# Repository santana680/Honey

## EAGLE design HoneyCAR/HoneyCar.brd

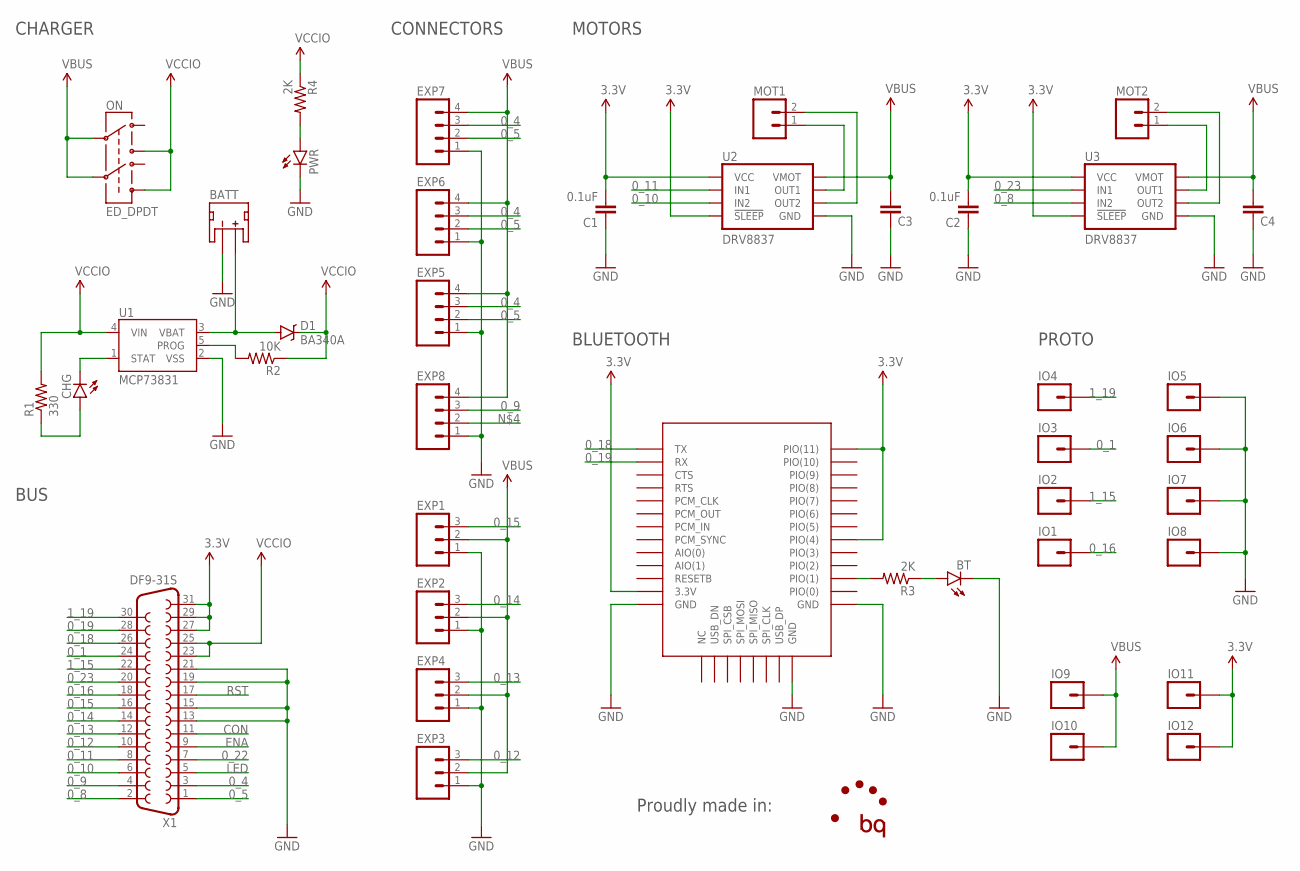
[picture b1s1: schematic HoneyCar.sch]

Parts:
BATT: JST_2MM_MALE; JST-2-SMD
BT: LED0603; LED-0603
C1, C2, C3, C4: 0.1uF; 0603-CAP
CHG: LED0603; LED-0603
D1: BA340A; SMA-DIODE
EXP1, EXP2, EXP3, EXP4: M03LOCK; 1X03_LOCK
EXP5, EXP6, EXP7, EXP8: M04JST; 1X04-1.5MM_JST
IC1: BC04_BLUETOOTH; BC04
IO1, IO2, IO3, IO4, IO5, IO6, IO7, IO8, IO9, IO10, IO11, IO12: M01PTH_LONGPAD; 1X01_LONGPAD
MOT1, MOT2: M02POLAR; MOLEX-1X2
ON: ED_DPDT
PWR: LED0603; LED-0603
R1: 330; R0402
R2: 10K; R0402
R3, R4: 2K; R0402
U1: MCP73831; SOT23-5
U2, U3: DRV8837; DSG
X1: DF9-31S

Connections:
0_1: IO3.1, X1.24
0_4: EXP5.3, EXP6.3, EXP7.3, X1.3
0_5: EXP5.2, EXP6.2, EXP7.2, X1.1
0_8: U3.5 (IN2), X1.2
0_9: EXP8.3, X1.4
0_10: U2.5 (IN2), X1.6
0_11: U2.6 (IN1), X1.8
0_12: EXP3.3, X1.10
0_13: EXP4.3, X1.12
0_14: EXP2.3, X1.14
0_15: EXP1.3, X1.16
0_16: IO1.1, X1.18
0_18: IC1.P$1 (TX), X1.26
0_19: IC1.P$2 (RX), X1.28
0_22: X1.7
0_23: U3.6 (IN1), X1.20
1_15: IO2.1, X1.22
1_19: IO4.1, X1.30
3.3V: C1.2, C2.2, IC1.P$12 (3.3V), IC1.P$27 (PIO(4)), IC1.P$34 (PIO(11)), IO11.1, IO12.1, U2.7 (!SLEEP), U2.8 (VCC), U3.7 (!SLEEP), U3.8 (VCC), X1.27, X1.29, X1.31
CON: X1.11
ENA: X1.9
GND: BATT.1 (-), BT.C, C1.1, C2.1, C3.1, C4.1, EXP1.1, EXP2.1, EXP3.1, EXP4.1, EXP5.1, EXP6.1, EXP7.1, EXP8.1, IC1.P$13 (GND), IC1.P$21 (GND), IC1.P$22 (GND), IO5.1, IO6.1, IO7.1, IO8.1, PWR.C, U1.2 (VSS), U2.4 (GND), U2.PAD (GND), U3.4 (GND), U3.PAD (GND), X1.13, X1.15, X1.19, X1.21
LED: X1.5
unnamed: IC1.P$24 (PIO(1)), R3.2
unnamed: BT.A, R3.1
unnamed: PWR.A, R4.2
unnamed: CHG.C, U1.1 (STAT)
unnamed: CHG.A, R1.1
unnamed: R2.2, U1.5 (PROG)
unnamed: BATT.2 (+), D1.A, U1.3 (VBAT)
unnamed: MOT1.1, U2.2 (OUT1)
unnamed: MOT1.2, U2.3 (OUT2)
unnamed: MOT2.1, U3.2 (OUT1)
unnamed: MOT2.2, U3.3 (OUT2)
RST: X1.17
VBUS: C3.2, C4.2, EXP1.2, EXP2.2, EXP3.2, EXP4.2, EXP5.4, EXP6.4, EXP7.4, EXP8.4, IO9.1, IO10.1, ON.2, ON.5, U2.1 (VMOT), U3.1 (VMOT)
VCCIO: D1.C, ON.3, ON.6, R1.2, R2.1, R4.1, U1.4 (VIN), X1.23, X1.25

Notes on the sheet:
CHARGER
BUS
MOTORS
CONNECTORS
BLUETOOTH
Proudly made in:
PROTO

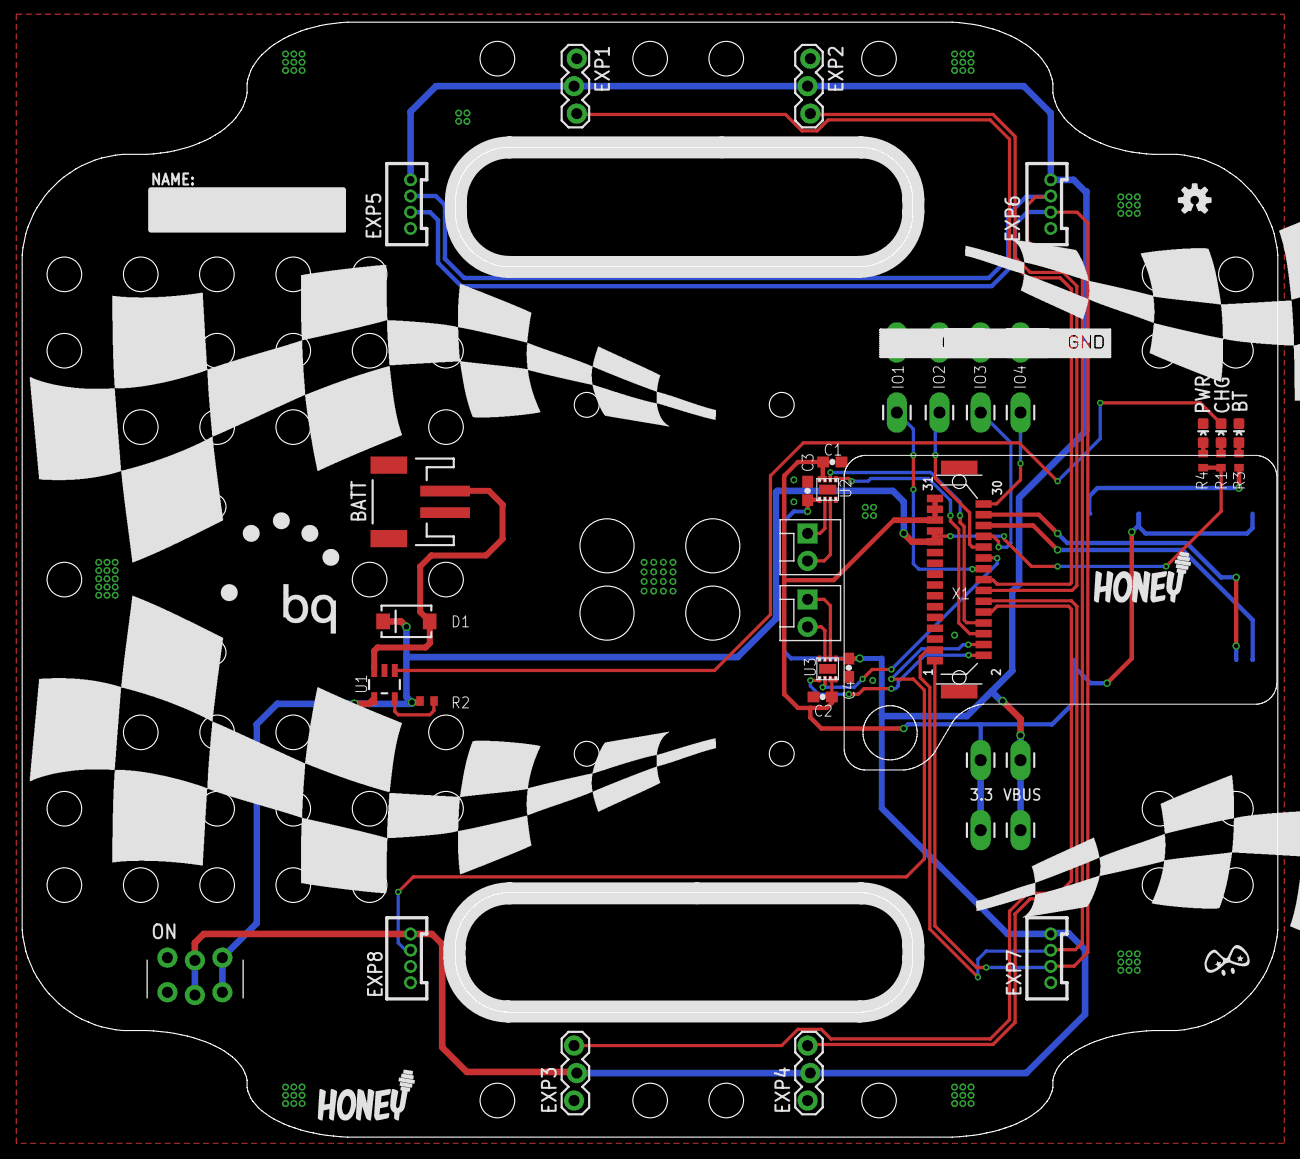
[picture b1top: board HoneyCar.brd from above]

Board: 2 copper layers, 116.1 x 103.1 mm, 52 parts (1 on the bottom side), 32 nets.

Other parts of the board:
LOGO1: OSHW-LOGOS; OSHW-LOGO-S
U$5, U$7: LOGO_MEDIUM
U$8: BQ_LOGO
U$9: PIGHIXXX_LOGO
U$10, U$11, U$12: S_KICIK_GND_1
U$14, U$15, U$16: CAR_RACING_BIG

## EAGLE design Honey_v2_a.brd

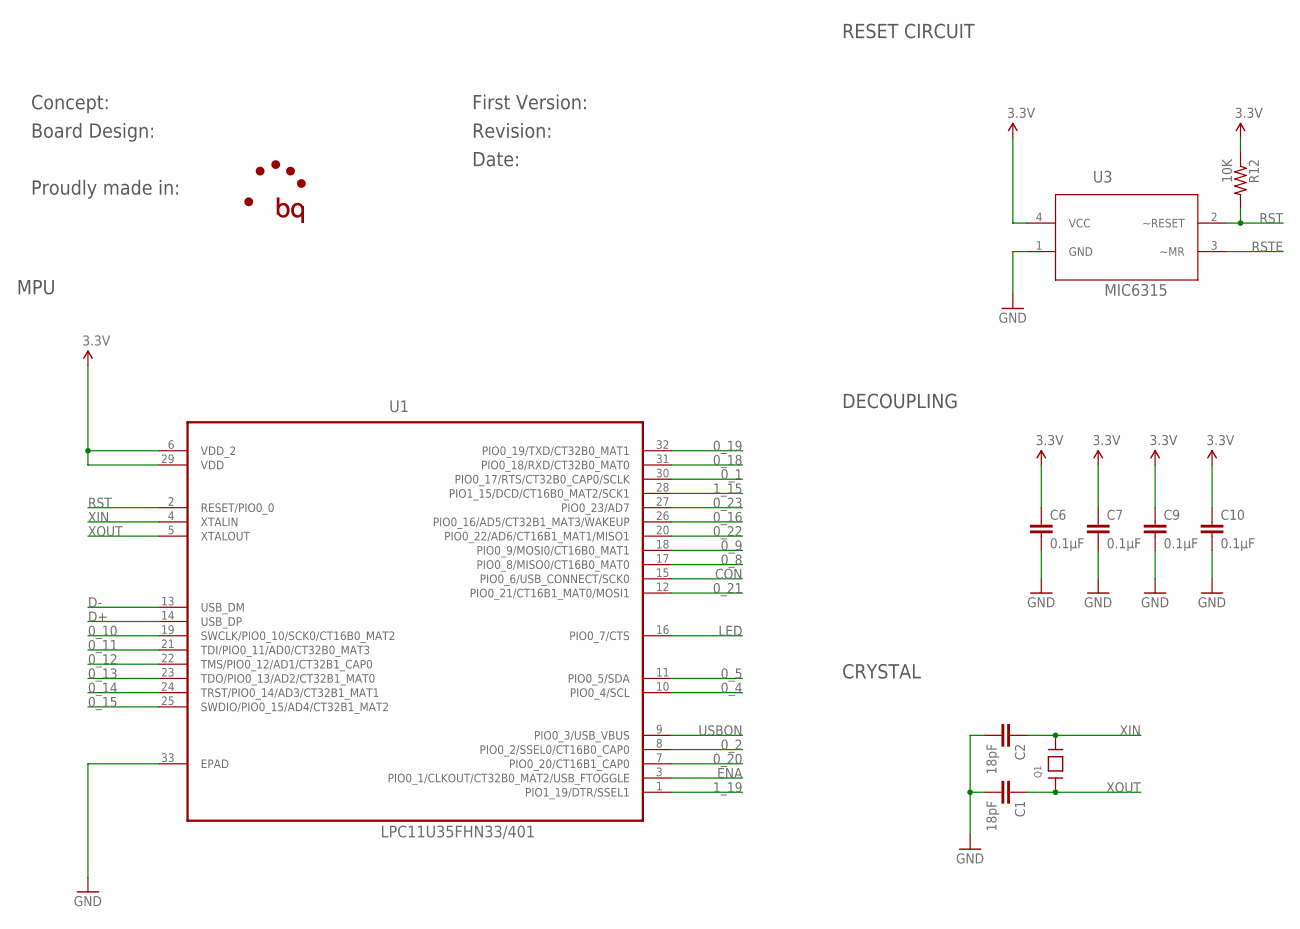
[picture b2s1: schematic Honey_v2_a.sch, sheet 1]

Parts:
C1, C2: 18pF; C0402
C6, C7, C9, C10: 0.1µF; C0402
Q1: 12MHz 4 pad crystal 3.2x2.5; CRYSTAL_3.2X2.5
R12: 10K; R0402
U1: LPC11U35FHN33/401; QFN65P700X700X100-33N
U3: MIC6315; SOT-143B

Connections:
0_1: U1.30 (PIO0_17/RTS/CT32B0_CAP0/SCLK); also elsewhere on the board
0_2: U1.8 (PIO0_2/SSEL0/CT16B0_CAP0)
0_4: U1.10 (PIO0_4/SCL); also elsewhere on the board
0_5: U1.11 (PIO0_5/SDA); also elsewhere on the board
0_8: U1.17 (PIO0_8/MISO0/CT16B0_MAT0); also elsewhere on the board
0_9: U1.18 (PIO0_9/MOSI0/CT16B0_MAT1); also elsewhere on the board
0_10: U1.19 (SWCLK/PIO0_10/SCK0/CT16B0_MAT2); also elsewhere on the board
0_11: U1.21 (TDI/PIO0_11/AD0/CT32B0_MAT3); also elsewhere on the board
0_12: U1.22 (TMS/PIO0_12/AD1/CT32B1_CAP0); also elsewhere on the board
0_13: U1.23 (TDO/PIO0_13/AD2/CT32B1_MAT0); also elsewhere on the board
0_14: U1.24 (TRST/PIO0_14/AD3/CT32B1_MAT1); also elsewhere on the board
0_15: U1.25 (SWDIO/PIO0_15/AD4/CT32B1_MAT2); also elsewhere on the board
0_16: U1.26 (PIO0_16/AD5/CT32B1_MAT3/WAKEUP); also elsewhere on the board
0_18: U1.31 (PIO0_18/RXD/CT32B0_MAT0); also elsewhere on the board
0_19: U1.32 (PIO0_19/TXD/CT32B0_MAT1); also elsewhere on the board
0_20: U1.7 (PIO0_20/CT16B1_CAP0)
0_21: U1.12 (PIO0_21/CT16B1_MAT0/MOSI1)
0_22: U1.20 (PIO0_22/AD6/CT16B1_MAT1/MISO1); also elsewhere on the board
0_23: U1.27 (PIO0_23/AD7); also elsewhere on the board
1_15: U1.28 (PIO1_15/DCD/CT16B0_MAT2/SCK1); also elsewhere on the board
1_19: U1.1 (PIO1_19/DTR/SSEL1); also elsewhere on the board
3.3V: C6.1, C7.1, C9.1, C10.1, R12.1, U1.6 (VDD_2), U1.29 (VDD), U3.4 (VCC); also elsewhere on the board
CON: U1.15 (PIO0_6/USB_CONNECT/SCK0); also elsewhere on the board
D+: U1.14 (USB_DP); also elsewhere on the board
D-: U1.13 (USB_DM); also elsewhere on the board
ENA: U1.3 (PIO0_1/CLKOUT/CT32B0_MAT2/USB_FTOGGLE); also elsewhere on the board
GND: C1.2, C2.2, C6.2, C7.2, C9.2, C10.2, U1.33 (EPAD), U3.1 (GND); also elsewhere on the board
LED: U1.16 (PIO0_7/CTS); also elsewhere on the board
RST: R12.2, U1.2 (RESET/PIO0_0), U3.2 (~RESET); also elsewhere on the board
RSTE: U3.3 (~MR); also elsewhere on the board
USBON: U1.9 (PIO0_3/USB_VBUS); also elsewhere on the board
XIN: C2.1, Q1.3, U1.4 (XTALIN)
XOUT: C1.1, Q1.1, U1.5 (XTALOUT)

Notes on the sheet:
MPU
RESET CIRCUIT
DECOUPLING
CRYSTAL
Concept:
Board Design:
Proudly made in:
First Version:
Revision:
Date:

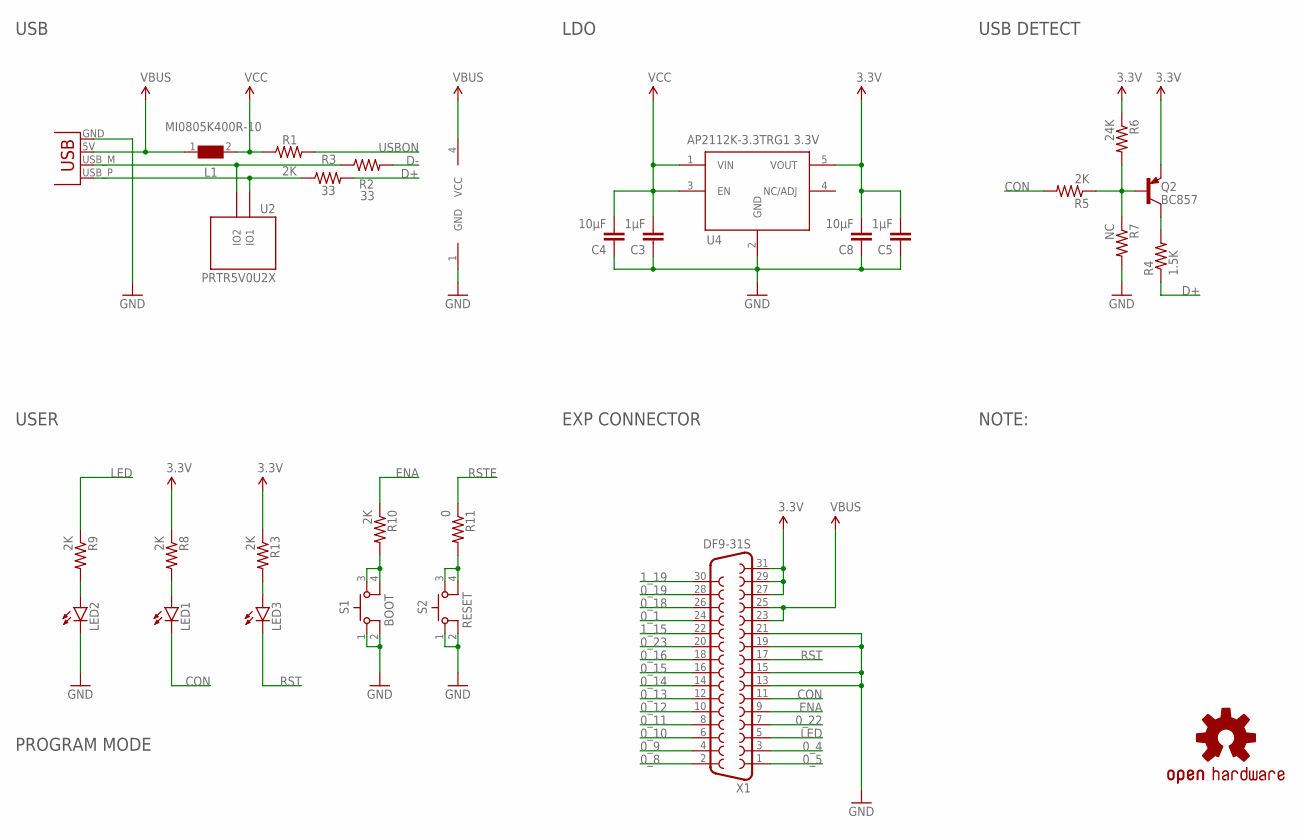
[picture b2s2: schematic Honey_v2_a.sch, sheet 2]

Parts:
C3, C5: 1µF; 0603-CAP
C4, C8: 10µF; 0603-CAP
J1: USBPCB; USB-A-PCB
L1: MI0805K400R-10; 0805
LED1, LED2, LED3: LED0603; LED-0603
LOGO1: OSHW-LOGOS; OSHW-LOGO-S
Q2: BC857; SOT23-BEC
R1, R5, R8, R9, R10, R13: 2K; R0402
R2, R3: 33; R0603
R4: 1.5K; R0402
R6: 24K; R0402
R7: NC; R0402
R11: 0; R0402
S1: BOOT; MINI_PUSHBUTTON
S2: RESET; MINI_PUSHBUTTON
U2: PRTR5V0U2X; SOT-143B
U4: AP2112K-3.3TRG1 3.3V; SOT23-5
X1: DF9-31S

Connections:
0_1: X1.24; also elsewhere on the board
0_4: X1.3; also elsewhere on the board
0_5: X1.1; also elsewhere on the board
0_8: X1.2; also elsewhere on the board
0_9: X1.4; also elsewhere on the board
0_10: X1.6; also elsewhere on the board
0_11: X1.8; also elsewhere on the board
0_12: X1.10; also elsewhere on the board
0_13: X1.12; also elsewhere on the board
0_14: X1.14; also elsewhere on the board
0_15: X1.16; also elsewhere on the board
0_16: X1.18; also elsewhere on the board
0_18: X1.26; also elsewhere on the board
0_19: X1.28; also elsewhere on the board
0_22: X1.7; also elsewhere on the board
0_23: X1.20; also elsewhere on the board
1_15: X1.22; also elsewhere on the board
1_19: X1.30; also elsewhere on the board
3.3V: C5.2, C8.2, Q2.E, R6.1, R8.1, R13.1, U4.5 (VOUT), X1.27, X1.29, X1.31; also elsewhere on the board
AD+: J1.USB_P (D+), R3.1, U2.2 (IO1)
AD-: J1.USB_M (D-), R2.1, U2.3 (IO2)
CON: LED1.C, R5.2, X1.11; also elsewhere on the board
D+: R3.2, R4.1; also elsewhere on the board
D-: R2.2; also elsewhere on the board
ENA: R10.1, X1.9; also elsewhere on the board
GND: C3.1, C4.1, C5.1, C8.1, J1.GND, LED2.C, R7.2, S1.1, S1.2, S2.1, S2.2, U2.1 (GND), U4.2 (GND), X1.13, X1.15, X1.19, X1.21; also elsewhere on the board
LED: R9.1, X1.5; also elsewhere on the board
unnamed: Q2.C, R4.2
unnamed: Q2.B, R5.1, R6.2, R7.1
unnamed: LED2.A, R9.2
unnamed: R10.2, S1.3, S1.4
unnamed: R11.2, S2.3, S2.4
unnamed: LED1.A, R8.2
unnamed: LED3.A, R13.2
RST: LED3.C, X1.17; also elsewhere on the board
RSTE: R11.1; also elsewhere on the board
USBON: R1.2; also elsewhere on the board
VBUS: J1.5V (VBUS), L1.1, U2.4 (VCC), X1.23, X1.25; also elsewhere on the board
VCC: C3.2, C4.2, L1.2, R1.1, U4.1 (VIN), U4.3 (EN)

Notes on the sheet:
USB
USER
LDO
USB DETECT
EXP CONNECTOR
PROGRAM MODE
NOTE:

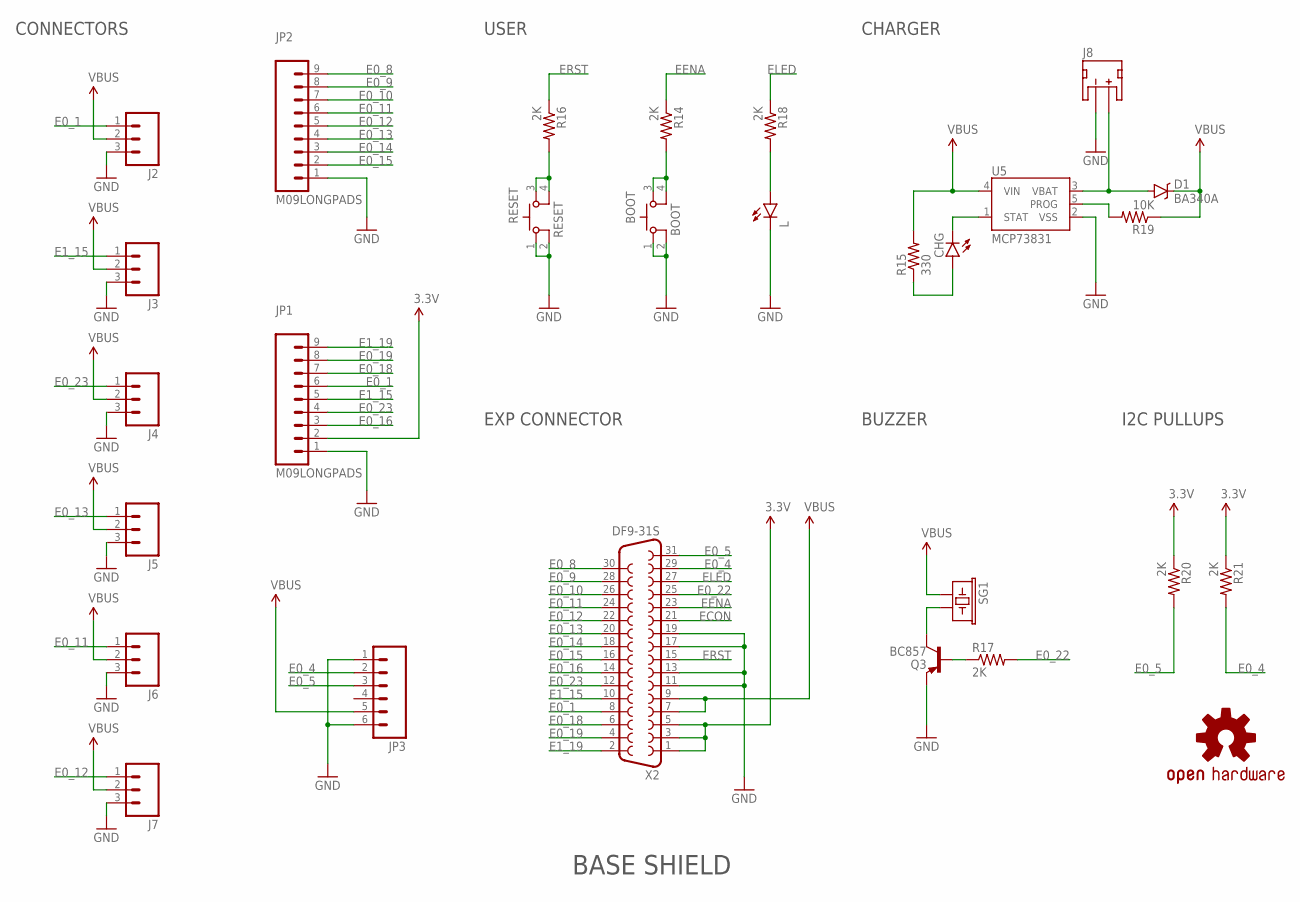
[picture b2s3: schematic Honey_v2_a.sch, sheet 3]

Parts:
BOOT: BOOT; MINI_PUSHBUTTON
CHG: LED0603; LED-0603
D1: BA340A; SMA-DIODE
J2, J3, J4, J5, J6, J7: M03LOCK_NO_SILK; 1X03_LOCK_NO_SILK
J8: JST_2MM_MALE; JST-2-SMD
JP1, JP2: M09LONGPADS; 1X09_LONGPADS
JP3: M06LONGPADS; 1X06_LONGPADS
L: LED0603; LED-0603
LOGO4: OSHW-LOGOS; OSHW-LOGO-S
Q3: BC857; SOT23-BEC
R14, R16, R17, R18, R20, R21: 2K; R0402
R15: 330; R0402
R19: 10K; R0402
RESET: RESET; MINI_PUSHBUTTON
SG1: BUZZERSMD2; BUZZER-CCV
U5: MCP73831; SOT23-5
X2: DF9-31S

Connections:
3.3V: JP1.2, R20.1, R21.1, X2.1, X2.3, X2.5; also elsewhere on the board
E0_1: J2.1, JP1.6, X2.8
E0_4: JP3.2, R21.2, X2.29
E0_5: JP3.3, R20.2, X2.31
E0_8: JP2.9, X2.30
E0_9: JP2.8, X2.28
E0_10: JP2.7, X2.26
E0_11: J6.1, JP2.6, X2.24
E0_12: J7.1, JP2.5, X2.22
E0_13: J5.1, JP2.4, X2.20
E0_14: JP2.3, X2.18
E0_15: JP2.2, X2.16
E0_16: JP1.3, X2.14
E0_18: JP1.7, X2.6
E0_19: JP1.8, X2.4
E0_22: R17.2, X2.25
E0_23: J4.1, JP1.4, X2.12
E1_15: J3.1, JP1.5, X2.10
E1_19: JP1.9, X2.2
ECON: X2.21
EENA: R14.1, X2.23
ELED: R18.1, X2.27
ERST: R16.1, X2.15
GND: BOOT.1, BOOT.2, J2.3, J3.3, J4.3, J5.3, J6.3, J7.3, J8.1 (-), JP1.1, JP2.1, JP3.1, JP3.6, L.C, Q3.E, RESET.1, RESET.2, U5.2 (VSS), X2.11, X2.13, X2.17, X2.19; also elsewhere on the board
unnamed: Q3.C, SG1.- (2)
unnamed: L.A, R18.2
unnamed: BOOT.3, BOOT.4, R14.2
unnamed: R16.2, RESET.3, RESET.4
unnamed: Q3.B, R17.1
unnamed: CHG.C, U5.1 (STAT)
unnamed: CHG.A, R15.1
unnamed: R19.2, U5.5 (PROG)
unnamed: D1.A, J8.2 (+), U5.3 (VBAT)
VBUS: D1.C, J2.2, J3.2, J4.2, J5.2, J6.2, J7.2, JP3.5, R15.2, R19.1, SG1.+ (1), U5.4 (VIN), X2.7, X2.9; also elsewhere on the board

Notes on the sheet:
CONNECTORS
USER
CHARGER
EXP CONNECTOR
BUZZER
BASE SHIELD
I2C PULLUPS

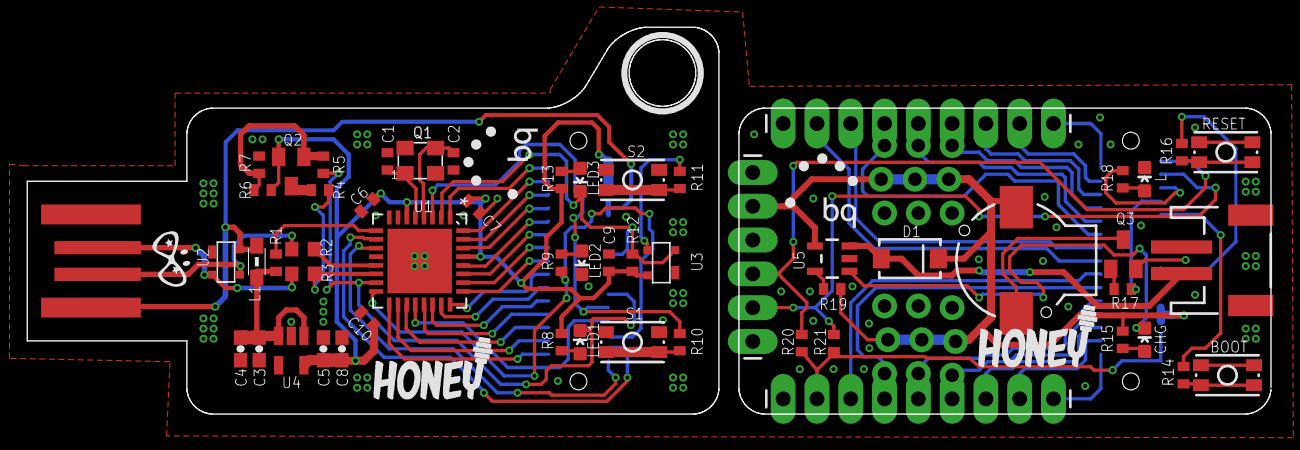
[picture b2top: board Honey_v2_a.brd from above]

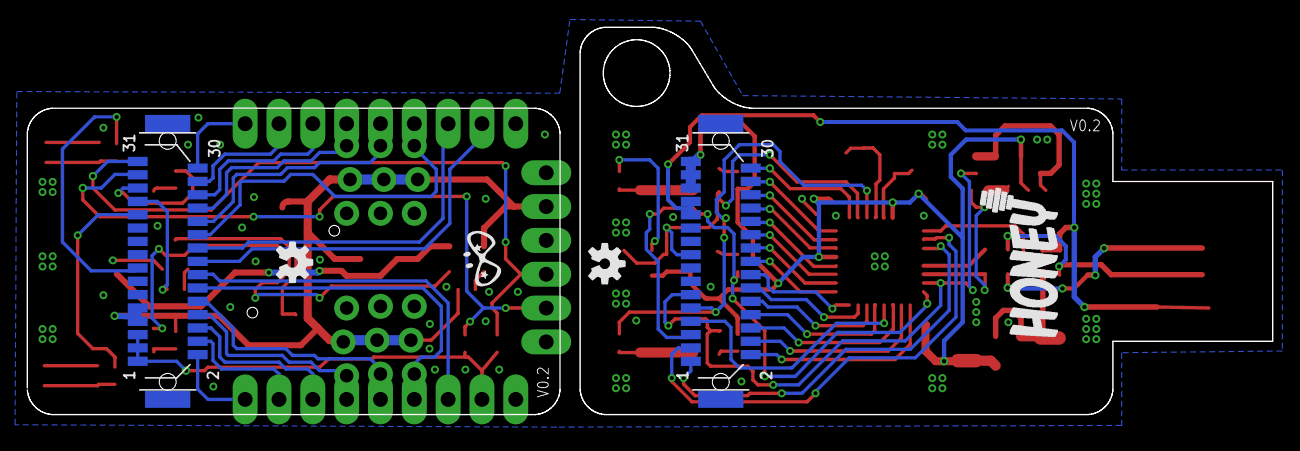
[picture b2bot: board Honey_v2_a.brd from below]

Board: 2 copper layers, 93.5 x 29.1 mm, 73 parts (6 on the bottom side), 71 nets.

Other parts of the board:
U$3, U$20: BQ_LOGO_SMALL
U$4, U$21: PIGHIXXX_LOGO
U$5, U$19: LOGO_MEDIUM
U$6: LOGO_BIG

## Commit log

2015-11-03 First revision
2015-11-03 HoneyCAR shield
2016-12-04 Create Hop 15-2

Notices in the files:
parts and their libraries:
SparkFun-PowerIC: Licensing: Creative Commons ShareAlike 4.0 International - https://creativecommons.org/licenses/by-sa/4.0
